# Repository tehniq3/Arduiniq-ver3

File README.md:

Arduiniq-ver3
=============

I present a personal version of Arduino board
look also at http://www.arduinotehniq.com/index.php/2017/05/11/home-arduino-arduiniq-ver-3-0/

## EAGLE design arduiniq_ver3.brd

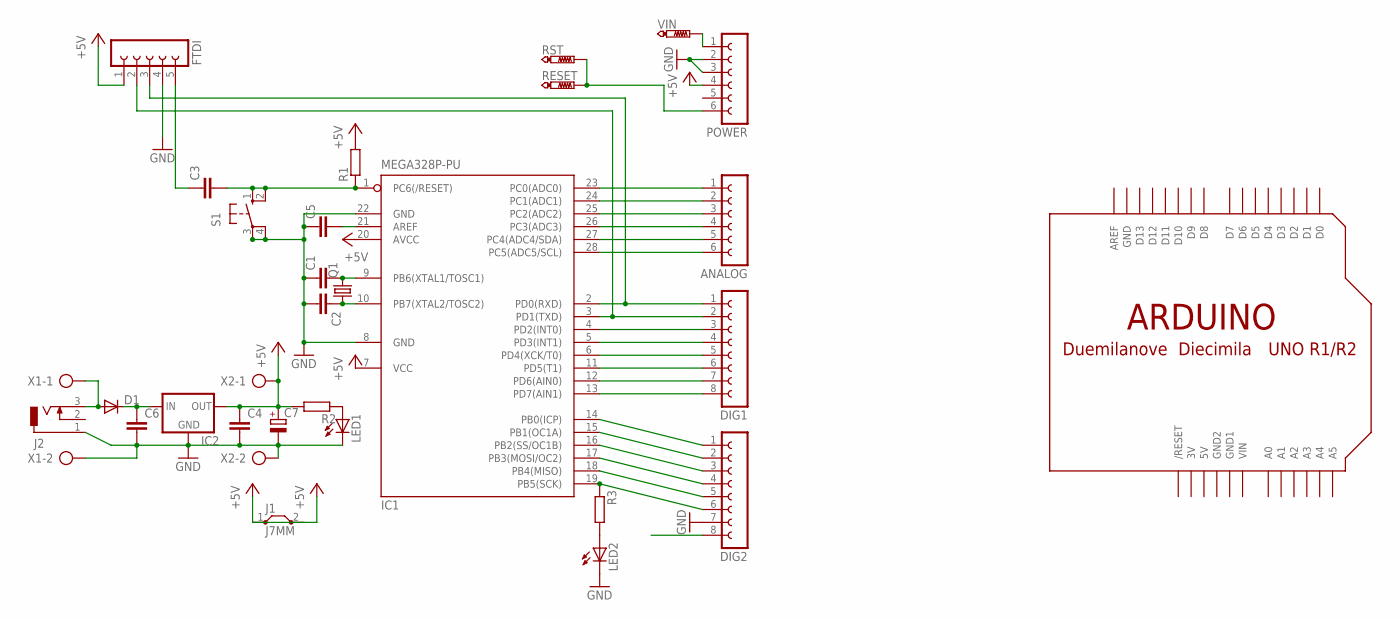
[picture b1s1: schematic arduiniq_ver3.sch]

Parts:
ANALOG: FE06-1; FE06
C1, C2, C3, C4, C5, C6: C-EU025-024X044; C025-024X044
C7: CPOL-EUE2.5-6; E2,5-6
D1: DO41-10
DIG1, DIG2: FE08-1; FE08
FTDI: FE05-1
IC1: MEGA328P-PU; DIL28-3
IC2: 78XXL
J1: J7MM; 07
J2: DCJ0303
LED1, LED2: LED5MM
POWER: FE06-1; FE06
Q1: CRYSTALHC49S; HC49/S
R1, R2: R-EU_0204/7; 0204/7
R3: R-EU_0207/10; 0207/10
RESET: PTR1PAD1-13Y; P1-13Y
RST: PTR1PAD1-13Y; P1-13Y
S1: 10-XX; B3F-10XX
U$1: ARDUINO-BPLACE
VIN: PTR1PAD1-13Y; P1-13Y
X1, X2: AK500/2

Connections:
3V: U$1.3V
+5V: C4.1, C7.+, FTDI.1, IC1.7 (VCC), IC1.20 (AVCC), IC2.OUT, J1.1, J1.2, POWER.4, R1.2, R2.2, U$1.5V, X2.1
AREF: C5.2, DIG2.8, IC1.21 (AREF)
GND: C1.1, C2.2, C4.2, C5.1, C6.2, C7.-, DIG2.7, FTDI.4, IC1.8 (GND), IC1.22 (GND), IC2.GND, J2.1, LED1.K (C), LED2.K (C), POWER.2, POWER.3, S1.3, S1.4 (P1), U$1.GND, X1.2, X2.2
GND1: U$1.GND1
GND2: U$1.GND2
unnamed: ANALOG.1, IC1.23 (PC0(ADC0))
unnamed: POWER.1, VIN.TP
unnamed: ANALOG.3, IC1.25 (PC2(ADC2))
unnamed: ANALOG.2, IC1.24 (PC1(ADC1))
unnamed: ANALOG.5, IC1.27 (PC4(ADC4/SDA))
unnamed: ANALOG.6, IC1.28 (PC5(ADC5/SCL))
unnamed: ANALOG.4, IC1.26 (PC3(ADC3))
unnamed: C1.2, IC1.9 (PB6(XTAL1/TOSC1)), Q1.2
unnamed: C3.1, FTDI.5
unnamed: DIG1.6, IC1.11 (PD5(T1))
unnamed: D1.A, J2.3, X1.1
unnamed: DIG2.2, IC1.15 (PB1(OC1A))
unnamed: DIG1.1, FTDI.3, IC1.2 (PD0(RXD))
unnamed: DIG1.2, FTDI.2, IC1.3 (PD1(TXD))
unnamed: DIG1.3, IC1.4 (PD2(INT0))
unnamed: DIG1.4, IC1.5 (PD3(INT1))
unnamed: DIG1.5, IC1.6 (PD4(XCK/T0))
unnamed: LED2.A, R3.2
unnamed: C6.1, D1.C, IC2.IN
unnamed: C2.1, IC1.10 (PB7(XTAL2/TOSC2)), Q1.1
unnamed: DIG1.7, IC1.12 (PD6(AIN0))
unnamed: DIG1.8, IC1.13 (PD7(AIN1))
unnamed: DIG2.1, IC1.14 (PB0(ICP))
unnamed: DIG2.3, IC1.16 (PB2(SS/OC1B))
unnamed: DIG2.4, IC1.17 (PB3(MOSI/OC2))
unnamed: DIG2.5, IC1.18 (PB4(MISO))
unnamed: DIG2.6, IC1.19 (PB5(SCK)), R3.1
unnamed: LED1.A, R2.1
RESET: C3.2, IC1.1 (PC6(/RESET)), POWER.6, R1.1, RESET.TP, RST.TP, S1.1 (S), S1.2 (S1)
VIN: U$1.VIN

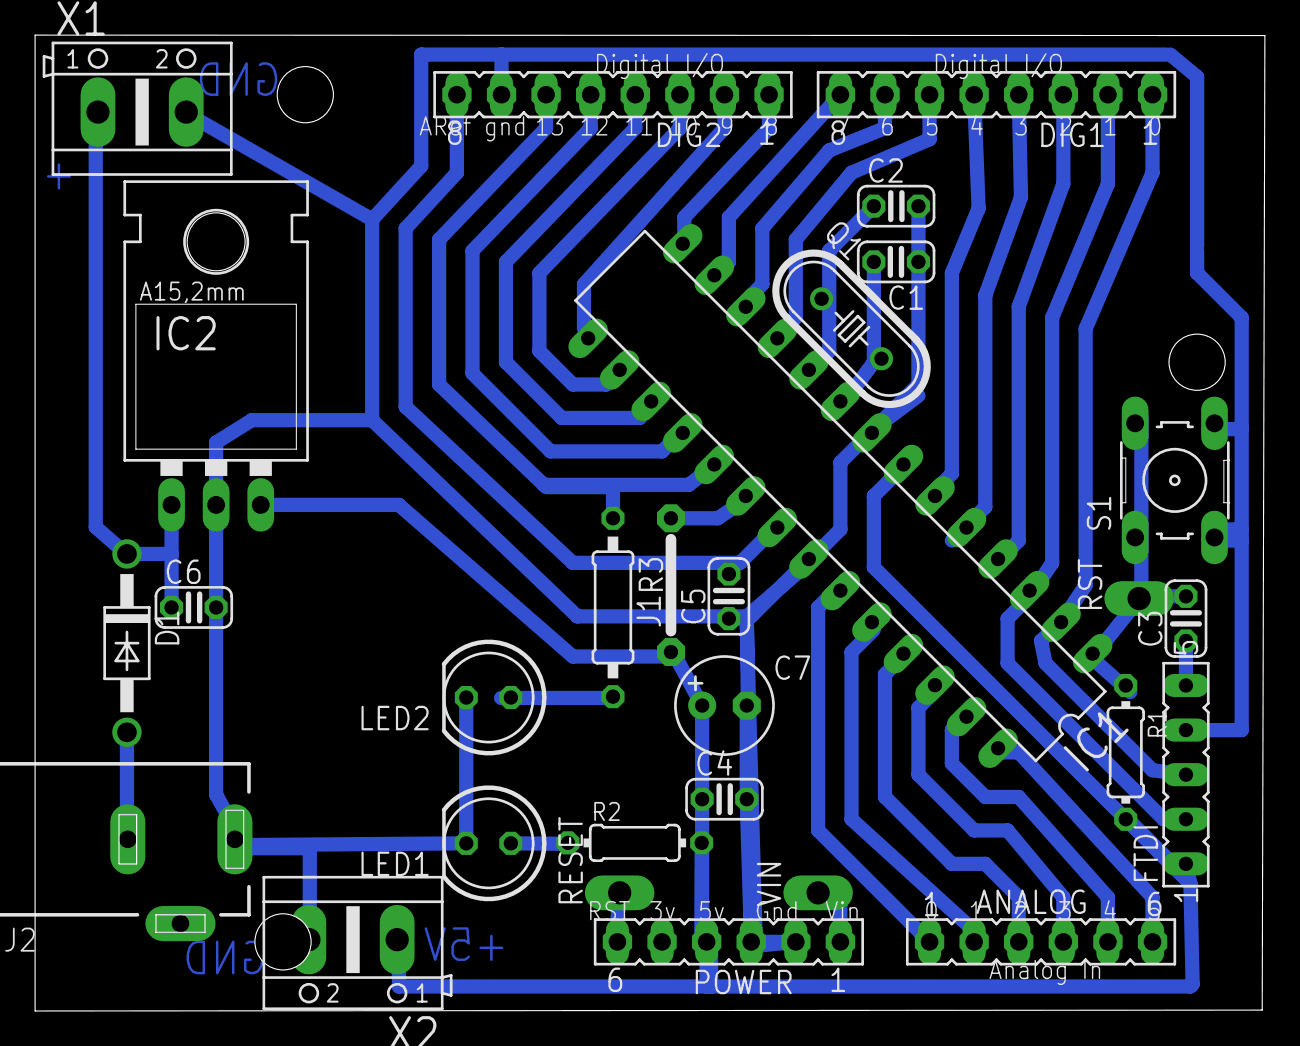
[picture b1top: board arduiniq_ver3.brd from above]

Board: 2 copper layers, 70.1 x 55.6 mm, 30 parts (0 on the bottom side), 32 nets.

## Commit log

2014-09-16 Create vasilica
